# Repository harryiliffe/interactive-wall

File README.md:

# Interactive Wall
A flexible system for creating an interactive wall

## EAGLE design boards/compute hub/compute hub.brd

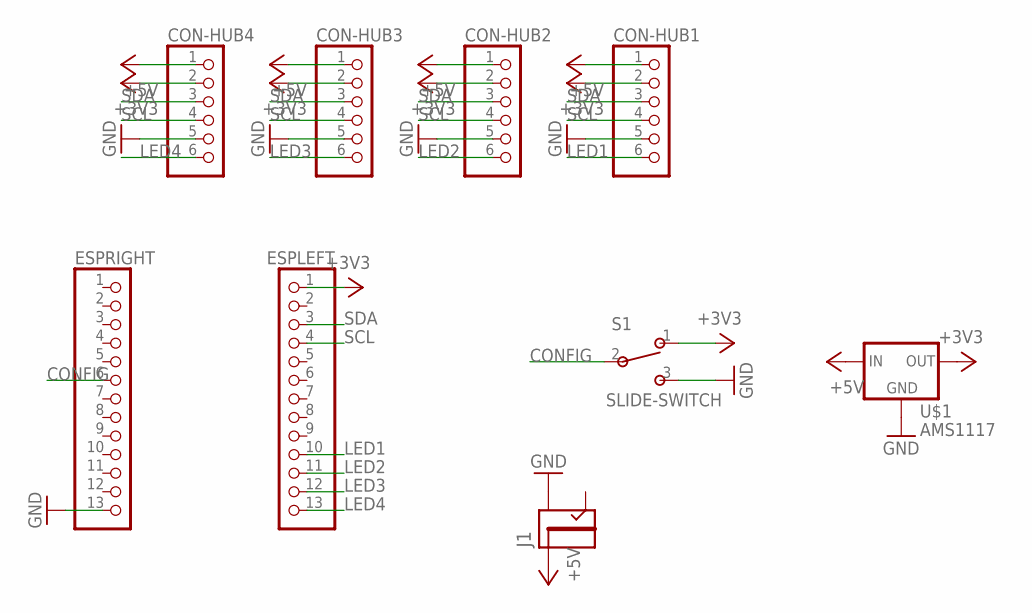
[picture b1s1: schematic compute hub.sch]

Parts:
CON-HUB1, CON-HUB2, CON-HUB3, CON-HUB4: PINHD-1X6; 1X06
ESPLEFT: PINHD-1X13; 1X13
ESPRIGHT: PINHD-1X13; 1X13
J1: JACK2.1MM; JACK_2.1MM
S1: SLIDE-SWITCH; AYZ0102AGRLC
U$1: AMS1117; SOT223

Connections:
+3V3: CON-HUB1.2, CON-HUB2.2, CON-HUB3.2, CON-HUB4.2, ESPLEFT.1, S1.1, U$1.2 (OUT)
+5V: CON-HUB1.1, CON-HUB2.1, CON-HUB3.1, CON-HUB4.1, J1.PIN, U$1.3 (IN)
CONFIG: ESPRIGHT.6, S1.2
GND: CON-HUB1.5, CON-HUB2.5, CON-HUB3.5, CON-HUB4.5, ESPRIGHT.13, J1.SHUNT, S1.3, U$1.1 (GND)
LED1: CON-HUB1.6, ESPLEFT.10
LED2: CON-HUB2.6, ESPLEFT.11
LED3: CON-HUB3.6, ESPLEFT.12
LED4: CON-HUB4.6, ESPLEFT.13
SCL: CON-HUB1.4, CON-HUB2.4, CON-HUB3.4, CON-HUB4.4, ESPLEFT.4
SDA: CON-HUB1.3, CON-HUB2.3, CON-HUB3.3, CON-HUB4.3, ESPLEFT.3

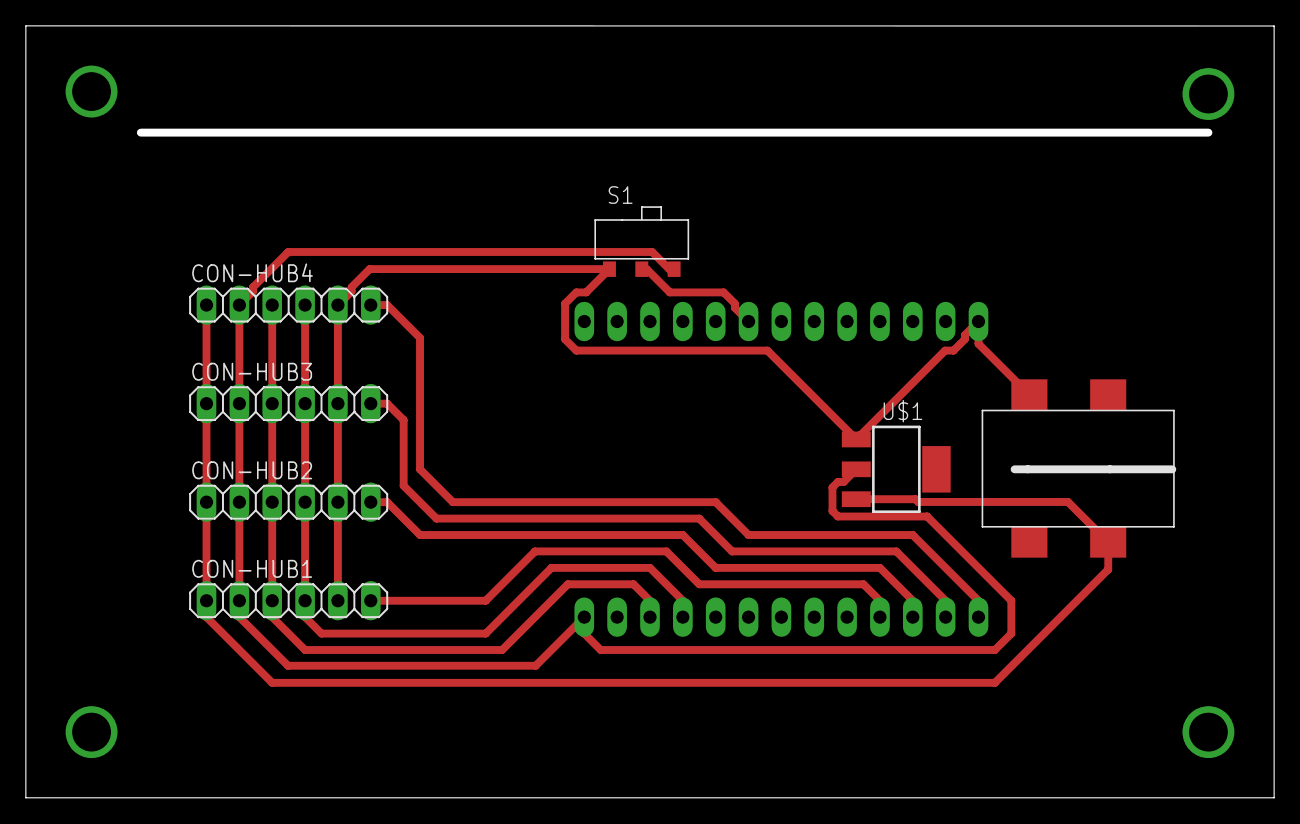
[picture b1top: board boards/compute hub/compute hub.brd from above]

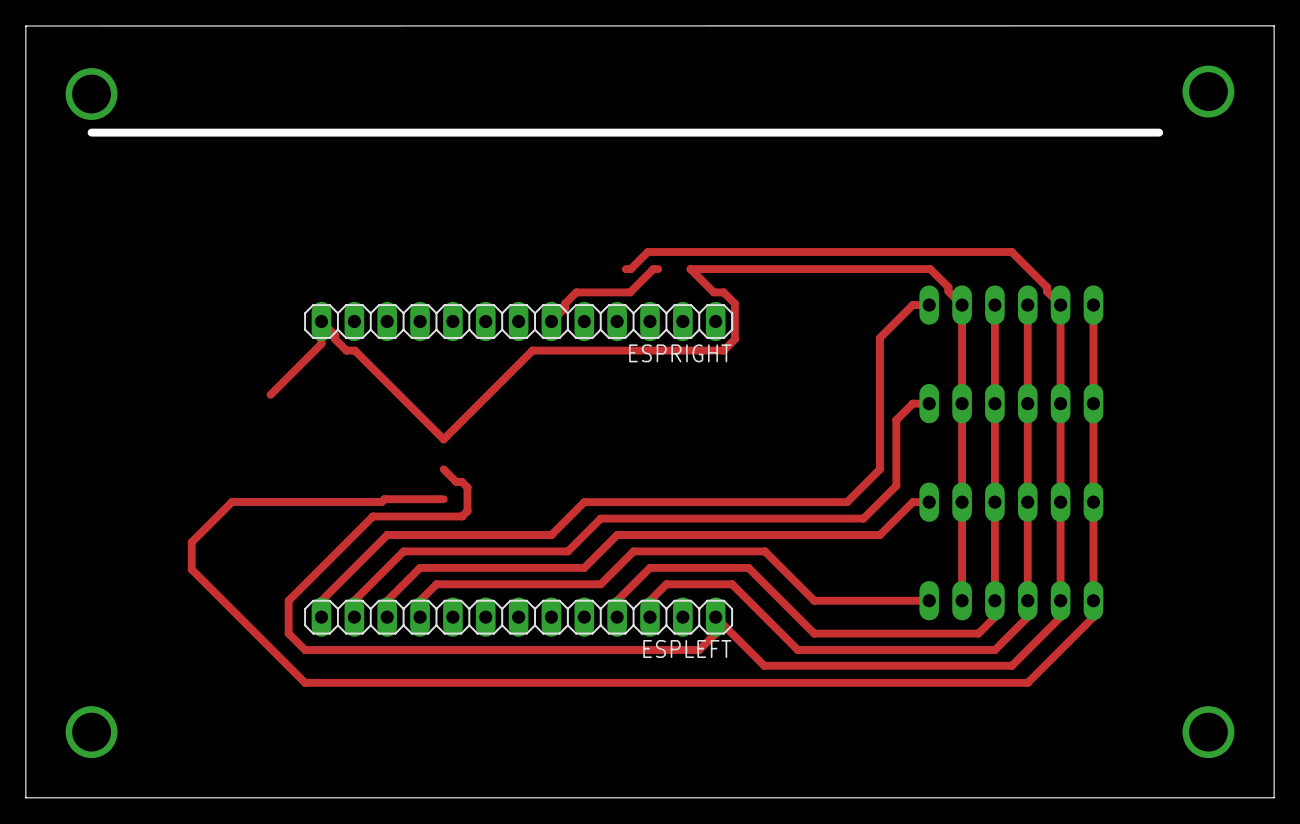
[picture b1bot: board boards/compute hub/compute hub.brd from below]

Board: 2 copper layers, 96.5 x 59.7 mm, 9 parts (2 on the bottom side), 10 nets.

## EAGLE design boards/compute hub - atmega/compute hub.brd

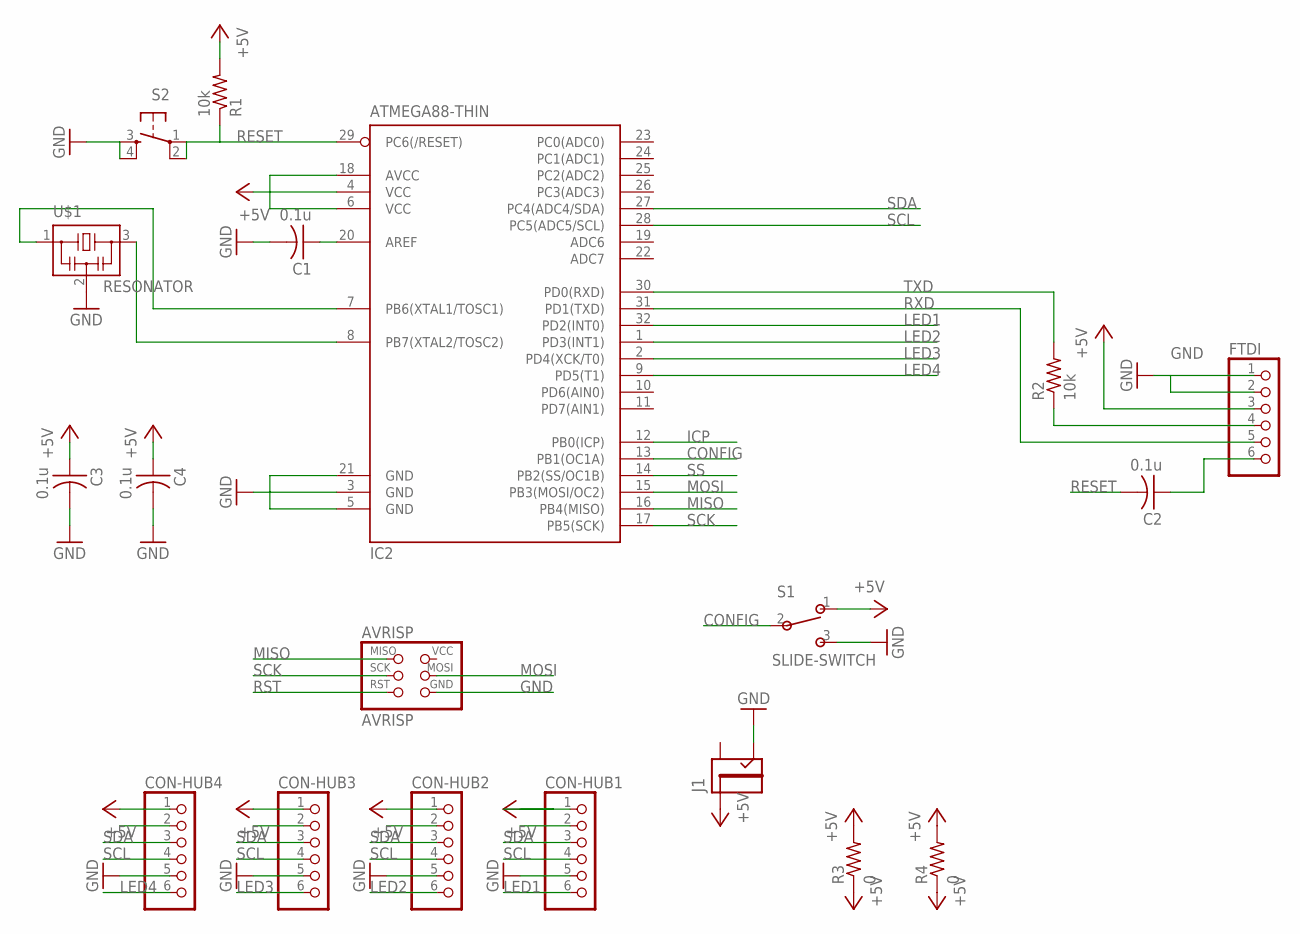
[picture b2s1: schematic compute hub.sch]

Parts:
AVRISP: AVRISP; 2X03
C1, C2, C3, C4: 0.1u; C1206FAB
CON-HUB1, CON-HUB2, CON-HUB3, CON-HUB4: PINHD-1X6; 1X06
FTDI: PINHD-1X6; 1X06
IC2: ATMEGA88-THIN; TQFP32-08THIN
J1: JACK2.1MM; JACK_2.1MM
R1, R2: 10k; R1206FAB
R3, R4: 0; R1206FAB
S1: SLIDE-SWITCH; AYZ0102AGRLC
S2: 6MM_SWITCH6MM_SWITCH; 6MM_SWITCH
U$1: RESONATOR; EFOBM

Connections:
+5V: C3.1, C4.1, CON-HUB1.1, CON-HUB2.1, CON-HUB3.1, CON-HUB4.1, FTDI.3, IC2.4 (VCC), IC2.6 (VCC), IC2.18 (AVCC), J1.PIN, R1.2, R3.1, R3.2, R4.1, R4.2
CONFIG: IC2.13 (PB1(OC1A)), S1.2
GND: AVRISP.6 (GND), C1.2, C3.2, C4.2, CON-HUB1.5, CON-HUB2.5, CON-HUB3.5, CON-HUB4.5, FTDI.1, FTDI.2, IC2.3 (GND), IC2.5 (GND), IC2.21 (GND), J1.CONTACT, S1.3, S2.3 (S), S2.4 (S1), U$1.2
ICP: IC2.12 (PB0(ICP))
LED1: CON-HUB1.6, IC2.32 (PD2(INT0))
LED2: CON-HUB2.6, IC2.1 (PD3(INT1))
LED3: CON-HUB3.6, IC2.2 (PD4(XCK/T0))
LED4: CON-HUB4.6, IC2.9 (PD5(T1))
MISO: AVRISP.1 (MISO), IC2.16 (PB4(MISO))
MOSI: AVRISP.4 (MOSI), IC2.15 (PB3(MOSI/OC2))
unnamed: C1.1, IC2.20 (AREF)
unnamed: IC2.8 (PB7(XTAL2/TOSC2)), U$1.3
unnamed: IC2.7 (PB6(XTAL1/TOSC1)), U$1.1
unnamed: FTDI.4, R2.1
unnamed: C2.1, FTDI.6
RESET: C2.2, IC2.29 (PC6(/RESET)), R1.1, S2.1, S2.2 (P1)
RST: AVRISP.5 (RST)
RXD: FTDI.5, IC2.31 (PD1(TXD))
SCK: AVRISP.3 (SCK), IC2.17 (PB5(SCK))
SCL: CON-HUB1.4, CON-HUB2.4, CON-HUB3.4, CON-HUB4.4, IC2.28 (PC5(ADC5/SCL))
SDA: CON-HUB1.3, CON-HUB2.3, CON-HUB3.3, CON-HUB4.3, IC2.27 (PC4(ADC4/SDA))
SS: IC2.14 (PB2(SS/OC1B))
TXD: IC2.30 (PD0(RXD)), R2.2

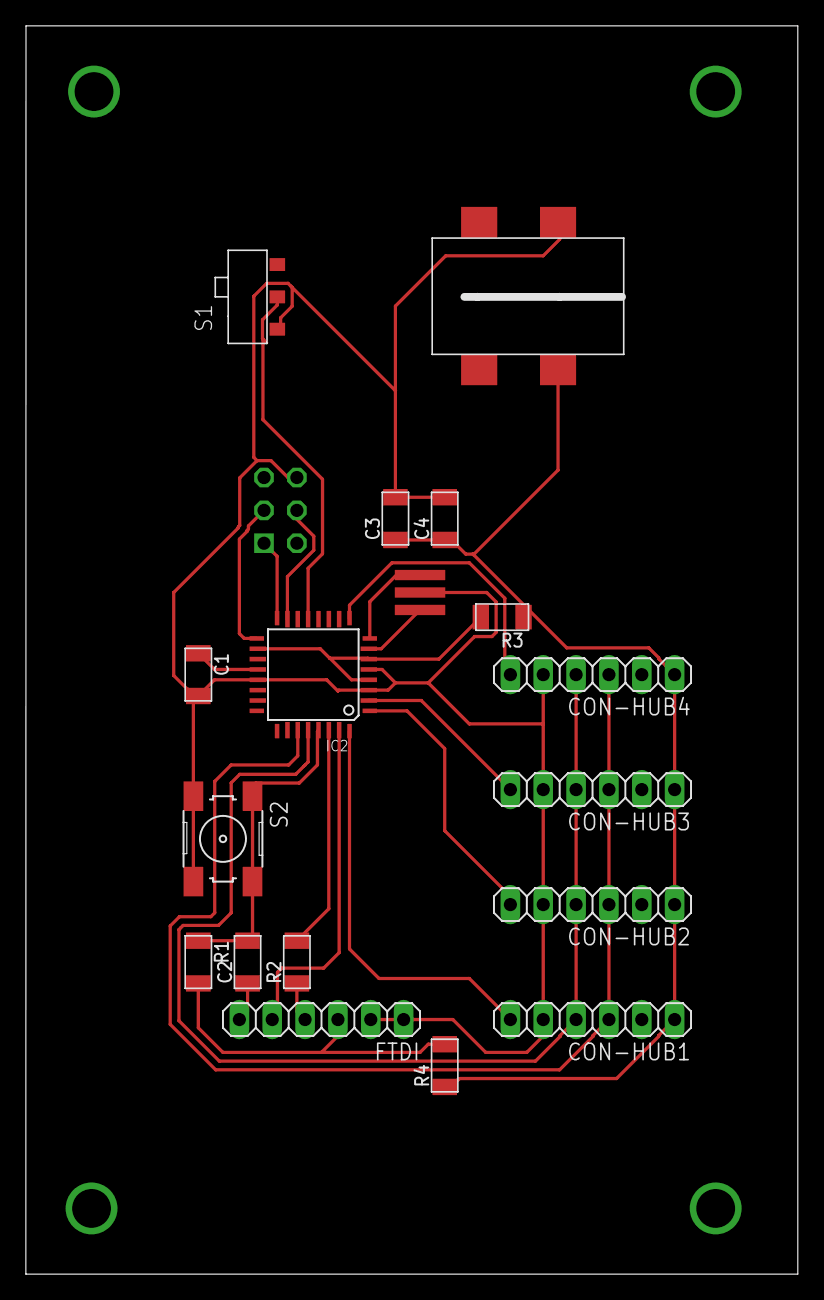
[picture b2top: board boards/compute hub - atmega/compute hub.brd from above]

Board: 2 copper layers, 59.7 x 96.5 mm, 19 parts (1 on the bottom side), 20 nets.

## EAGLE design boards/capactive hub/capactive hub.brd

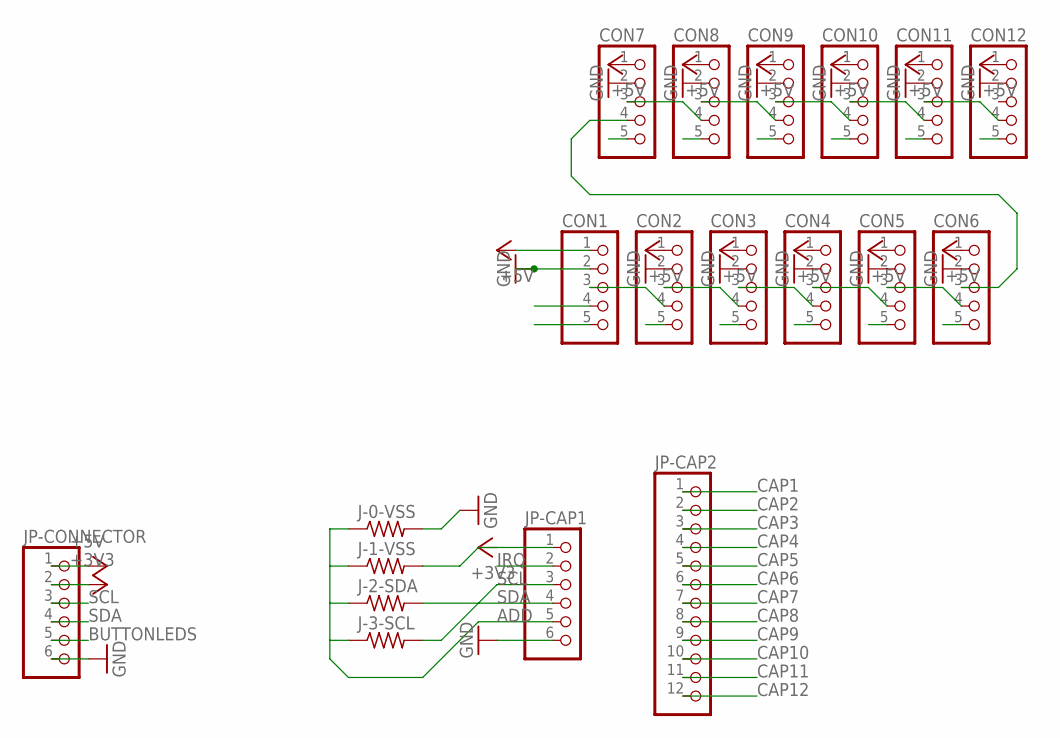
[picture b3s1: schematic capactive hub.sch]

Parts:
CON1, CON2, CON3, CON4, CON5, CON6, CON7, CON8, CON9, CON10, CON11, CON12: PINHD-1X5; 1X05
J-0-VSS, J-1-VSS, J-2-SDA, J-3-SCL: RES-US1206FAB; R1206FAB
JP-CAP1: PINHD-1X6; 1X06
JP-CAP2: PINHD-1X12; 1X12
JP-CONNECTOR: PINHD-1X6; 1X06

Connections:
+3V3: J-1-VSS.2, JP-CAP1.1, JP-CONNECTOR.2
+5V: CON1.1, CON2.1, CON3.1, CON4.1, CON5.1, CON6.1, CON7.1, CON8.1, CON9.1, CON10.1, CON11.1, CON12.1, JP-CONNECTOR.1
ADD: J-0-VSS.1, J-1-VSS.1, J-2-SDA.1, J-3-SCL.1, JP-CAP1.5
BUTTONLEDS: CON1.4, JP-CONNECTOR.5
CAP1: CON1.5, JP-CAP2.1
CAP2: CON2.5, JP-CAP2.2
CAP3: CON3.5, JP-CAP2.3
CAP4: CON4.5, JP-CAP2.4
CAP5: CON5.5, JP-CAP2.5
CAP6: CON6.5, JP-CAP2.6
CAP7: CON7.5, JP-CAP2.7
CAP8: CON8.5, JP-CAP2.8
CAP9: CON9.5, JP-CAP2.9
CAP10: CON10.5, JP-CAP2.10
CAP11: CON11.5, JP-CAP2.11
CAP12: CON12.5, JP-CAP2.12
GND: CON1.2, CON2.2, CON3.2, CON4.2, CON5.2, CON6.2, CON7.2, CON8.2, CON9.2, CON10.2, CON11.2, CON12.2, J-0-VSS.2, JP-CAP1.6, JP-CONNECTOR.6
IRQ: JP-CAP1.2
LEDOUT: CON1.3, CON2.4
unnamed: CON2.3, CON3.4
unnamed: CON3.3, CON4.4
unnamed: CON4.3, CON5.4
unnamed: CON5.3, CON6.4
unnamed: CON6.3, CON7.4
unnamed: CON7.3, CON8.4
unnamed: CON8.3, CON9.4
unnamed: CON9.3, CON10.4
unnamed: CON10.3, CON11.4
unnamed: CON11.3, CON12.4
SCL: J-3-SCL.2, JP-CAP1.3, JP-CONNECTOR.3
SDA: J-2-SDA.2, JP-CAP1.4, JP-CONNECTOR.4

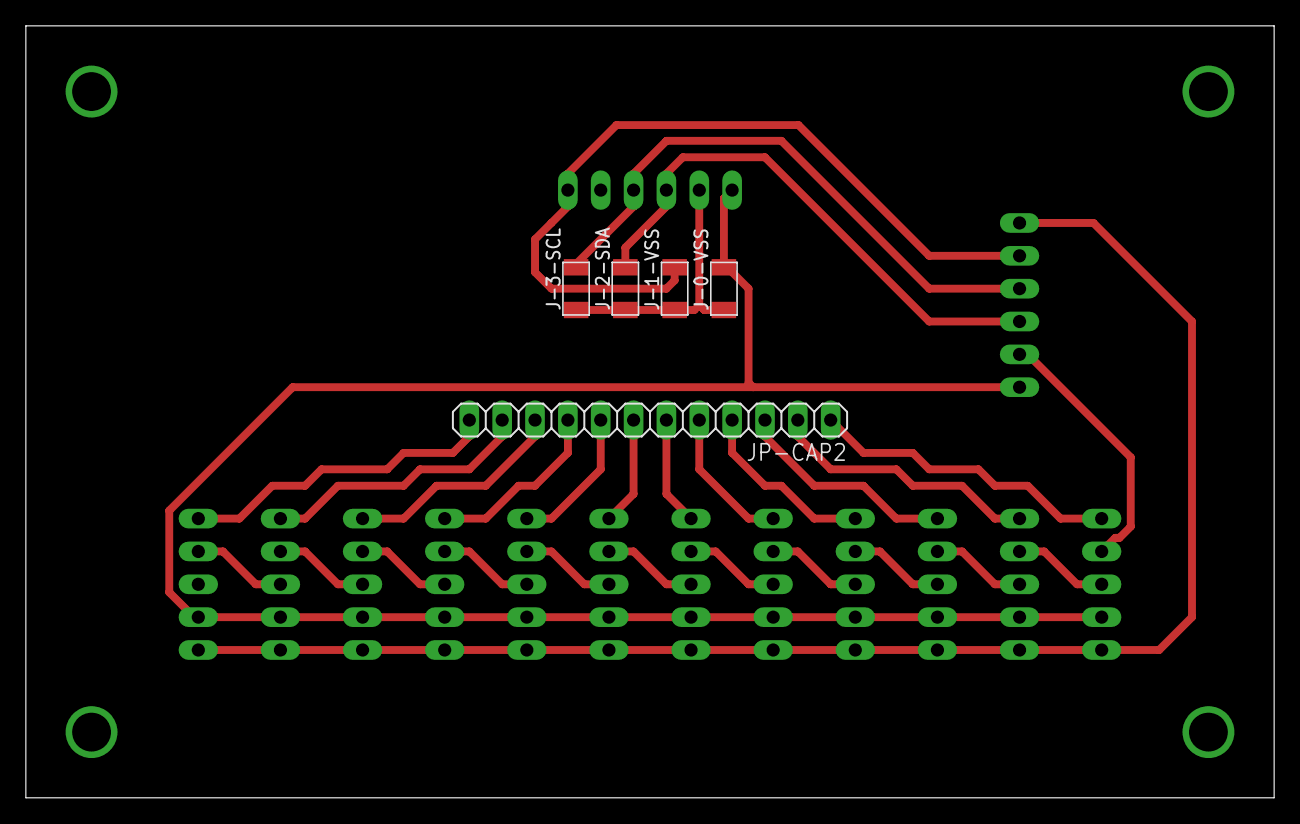
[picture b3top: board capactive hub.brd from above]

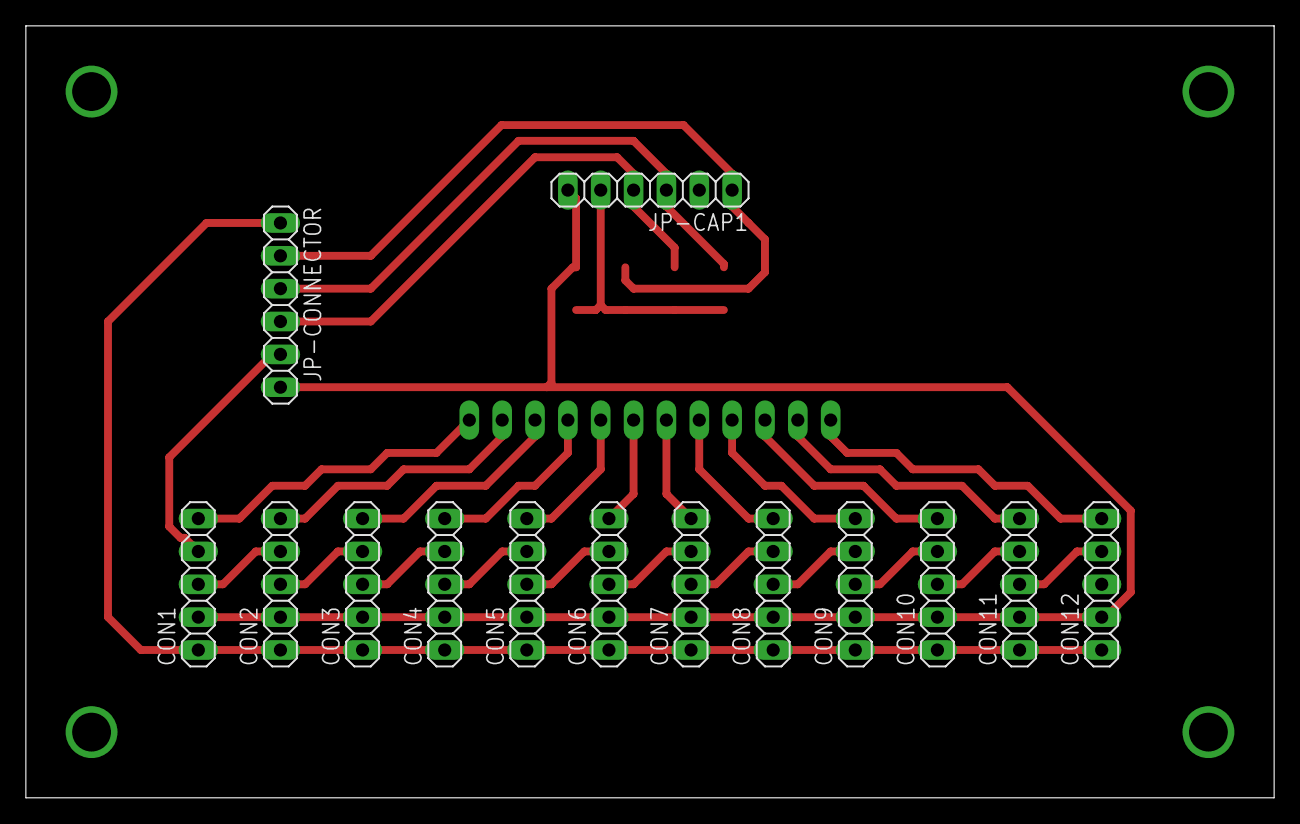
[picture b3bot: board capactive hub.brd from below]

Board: 2 copper layers, 96.5 x 59.7 mm, 19 parts (14 on the bottom side), 30 nets.

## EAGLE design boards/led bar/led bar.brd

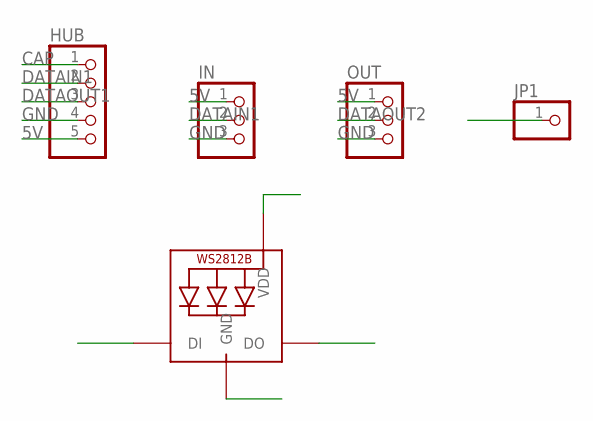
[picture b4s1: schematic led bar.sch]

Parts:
HUB: PINHD-1X5; 1X05
IN: PINHD-1X3; 1X03
JP1: PINHD-1X1; 1X01
LED1: WS2812B5050; WS2812B
OUT: PINHD-1X3; 1X03

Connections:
5V: HUB.5, IN.1, LED1.1-VDD (VDD), OUT.1
CAP: HUB.1
DATAIN1: HUB.2, IN.2, LED1.4-DIN (DI)
DATAOUT1: HUB.3, JP1.1
DATAOUT2: LED1.2-DOUT (DO), OUT.2
GND: HUB.4, IN.3, LED1.3-GND (GND), OUT.3

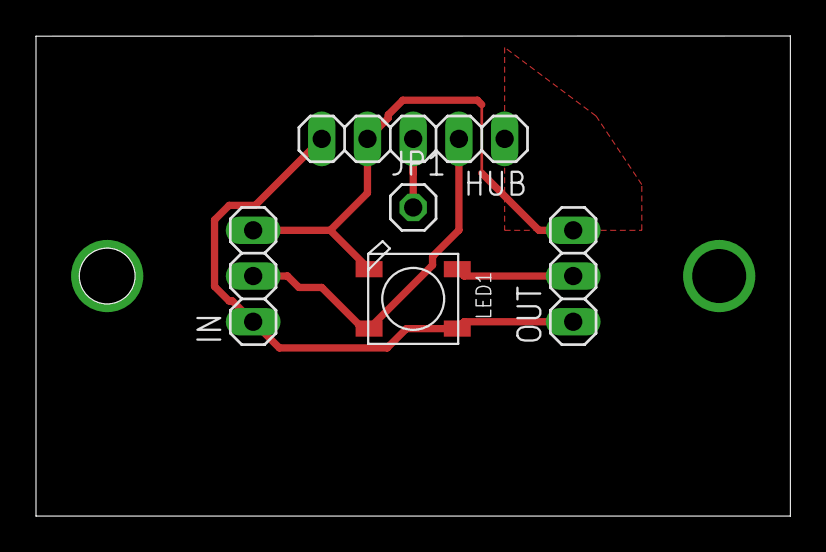
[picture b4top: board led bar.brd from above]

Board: 2 copper layers, 41.9 x 26.7 mm, 5 parts (0 on the bottom side), 5 nets.

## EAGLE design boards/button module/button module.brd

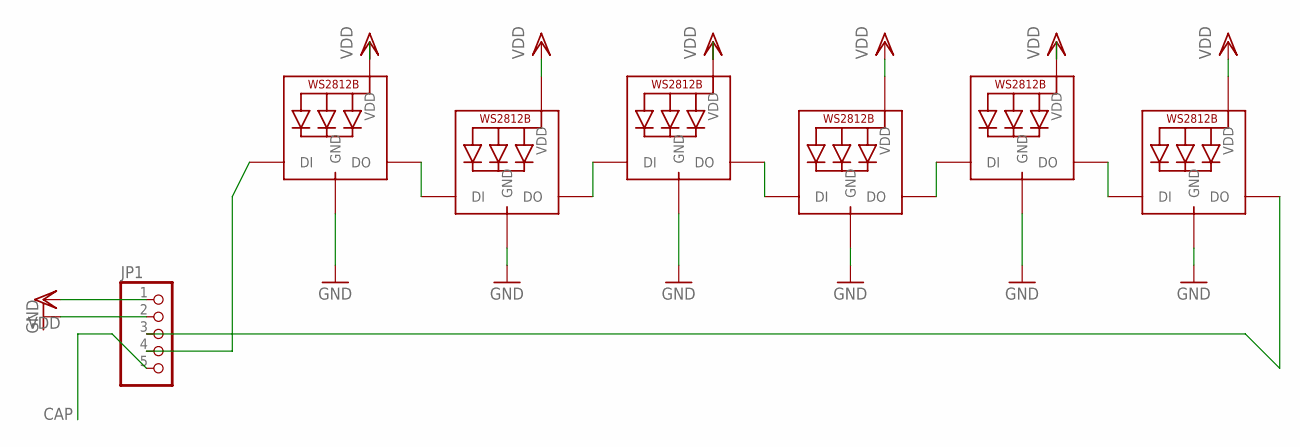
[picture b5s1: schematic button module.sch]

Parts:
JP1: PINHD-1X5; 1X05
LED1, LED2, LED3, LED4, LED5, LED6: WS2812B5050; WS2812B

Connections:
CAP: JP1.5
GND: JP1.2, LED1.3-GND (GND), LED2.3-GND (GND), LED3.3-GND (GND), LED4.3-GND (GND), LED5.3-GND (GND), LED6.3-GND (GND)
unnamed: JP1.4, LED1.4-DIN (DI)
unnamed: JP1.3, LED6.2-DOUT (DO)
unnamed: LED1.2-DOUT (DO), LED2.4-DIN (DI)
unnamed: LED2.2-DOUT (DO), LED3.4-DIN (DI)
unnamed: LED3.2-DOUT (DO), LED4.4-DIN (DI)
unnamed: LED4.2-DOUT (DO), LED5.4-DIN (DI)
unnamed: LED5.2-DOUT (DO), LED6.4-DIN (DI)
VDD: JP1.1, LED1.1-VDD (VDD), LED2.1-VDD (VDD), LED3.1-VDD (VDD), LED4.1-VDD (VDD), LED5.1-VDD (VDD), LED6.1-VDD (VDD)

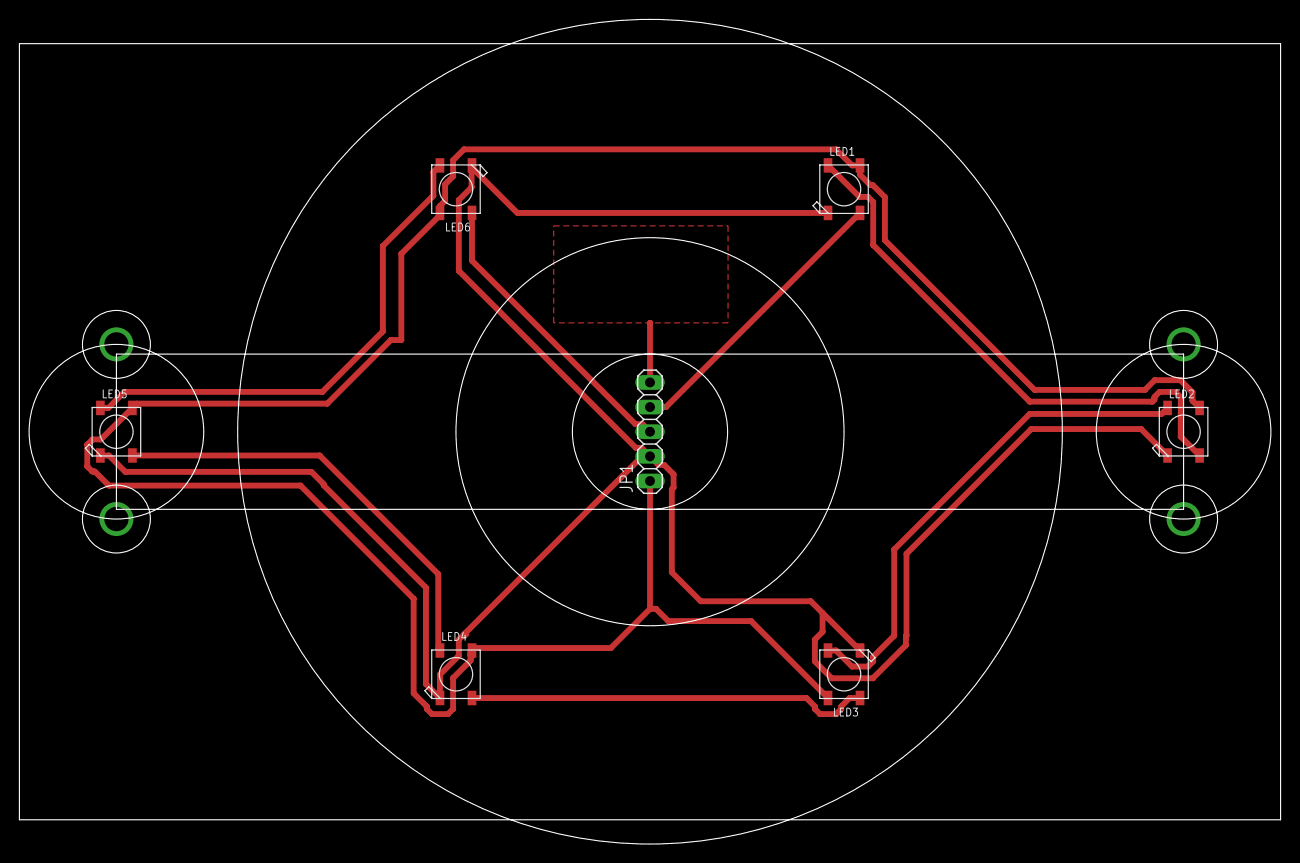
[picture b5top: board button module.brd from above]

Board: 2 copper layers, 130.0 x 85.0 mm, 7 parts (0 on the bottom side), 9 nets.

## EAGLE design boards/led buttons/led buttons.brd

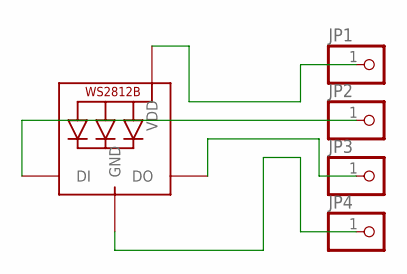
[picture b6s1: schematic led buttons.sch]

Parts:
JP1, JP2, JP3, JP4: PINHD-1X1; 1X01
LED1: WS2812B5050; WS2812B

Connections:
GND: JP4.1, LED1.3-GND (GND)
unnamed: JP1.1, LED1.1-VDD (VDD)
unnamed: JP3.1, LED1.2-DOUT (DO)
unnamed: JP2.1, LED1.4-DIN (DI)

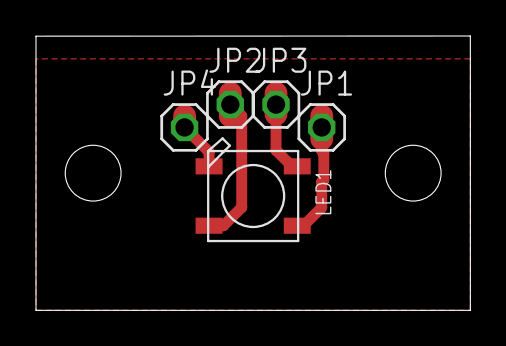
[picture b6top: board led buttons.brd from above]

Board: 2 copper layers, 24.1 x 15.2 mm, 5 parts (0 on the bottom side), 4 nets.

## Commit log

2018-11-16 added buildlog
2018-11-16 created basic i2c example
2018-11-16 added electronics and different button shapes
2018-11-30 updated docs and added more code tests
2018-12-03 Added Liz's section
2018-12-03 Added information
2018-12-04 added boards and extended materials list
2018-12-05 added main code
2018-12-05 updated configuration mode to add flashing
2018-12-09 documemtation updates
2018-12-09 moved electonics to seperate file and moved images.
2018-12-09 Form image
2018-12-09 Test
2018-12-09 Image added
2018-12-10 began naming conventions
2018-12-11 updated boards
2018-12-11 added images
2018-12-11 added guide
2018-12-13 added led bar support
2018-12-13 added info
2018-12-14 added Seeedunio code
2018-12-14 added led bar circuit board
2019-02-08 added atmega compute board
2019-02-11 updated circuit board designs
2019-03-11 updated circuits, added test files, fixed images.
2019-03-11 Added layout files, updated docs
2019-12-14 updated docs && circuit board
2019-12-14 Bump nokogiri from 1.8.1 to 1.10.7 in /docs
    Bumps [nokogiri](https://github.com/sparklemotion/nokogiri) from 1.8.1 to 1.10.7.
    - [Release notes](https://github.com/sparklemotion/nokogiri/releases)
    - [Changelog](https://github.com/sparklemotion/nokogiri/blob/master/CHANGELOG.md)
    - [Commits](https://github.com/sparklemotion/nokogiri/compare/v1.8.1...v1.10.7)
2019-12-14 Bump ffi from 1.9.18 to 1.11.3 in /docs
    Bumps [ffi](https://github.com/ffi/ffi) from 1.9.18 to 1.11.3.
    - [Release notes](https://github.com/ffi/ffi/releases)
    - [Changelog](https://github.com/ffi/ffi/blob/master/CHANGELOG.md)
    - [Commits](https://github.com/ffi/ffi/compare/1.9.18...1.11.3)
2020-02-25 Bump nokogiri from 1.8.1 to 1.10.8 in /docs
    Bumps [nokogiri](https://github.com/sparklemotion/nokogiri) from 1.8.1 to 1.10.8.
    - [Release notes](https://github.com/sparklemotion/nokogiri/releases)
    - [Changelog](https://github.com/sparklemotion/nokogiri/blob/master/CHANGELOG.md)
    - [Commits](https://github.com/sparklemotion/nokogiri/compare/v1.8.1...v1.10.8)
2021-05-19 Bump nokogiri from 1.8.1 to 1.11.4 in /docs
    Bumps [nokogiri](https://github.com/sparklemotion/nokogiri) from 1.8.1 to 1.11.4.
    - [Release notes](https://github.com/sparklemotion/nokogiri/releases)
    - [Changelog](https://github.com/sparklemotion/nokogiri/blob/main/CHANGELOG.md)
    - [Commits](https://github.com/sparklemotion/nokogiri/compare/v1.8.1...v1.11.4)
2021-07-13 Bump addressable from 2.5.2 to 2.8.0 in /docs
    Bumps [addressable](https://github.com/sporkmonger/addressable) from 2.5.2 to 2.8.0.
    - [Release notes](https://github.com/sporkmonger/addressable/releases)
    - [Changelog](https://github.com/sporkmonger/addressable/blob/main/CHANGELOG.md)
    - [Commits](https://github.com/sporkmonger/addressable/compare/addressable-2.5.2...addressable-2.8.0)
    ---
    updated-dependencies:
